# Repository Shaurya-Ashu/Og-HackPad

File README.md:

# Og-HackPad
Hello guys it's an Og HackPad for blueprint hack club . It controls the music and the vibe of the room it has three keyboard switches, 16 RGB LED and a volume controller with a small oled, displaying the name of the song .It's all controlled by XIAO R2040 the "BRAINS" and powered by US PC

# who am I?
Oh this is SHAURYA , I am a young inventor and passionate about cool robotic stuff so like I build multiple projects in my pass but not anything creative as cool as this one it's pretty damn cool. You know like RGB matrix flying up and down on with the song flow that's good.

# component used / BOM

| No. | Component | Qty | 
| --- | --------- | --- |
| 1   | XIAO R2040 | 1  |
| 2   | MX-Cherry switches | 3 |
| 3   | EC11 Rotary encoders | 1 |
| 4   | 0.91 inch OLED | 1 |
| 5   | SK6812 MINI-E LEDs | 16 |
| 6   | 3D PRINTED CASE  | 1 |
| 7   | PCB              | 1 |
| 8   | M3x16mm screws   | 4 |
| 9   | M3x5mx4mm heatset inserts | 4 |

# schematic 
So here are all the connections

--> The three switches are connected respectively to D10 D9 & D8 <br>
--> The rotary encoder is connected to D1 & D2 <br>
--> The old is connected to SCL & SDA respectively <br>
--> The RGB light is connected to D0 <br>

# PCB 
I have designed the PCB in KiCad
Finding all the models and footprint for a headache, but at last it's all done.

# CAD 
I have used fusion education for designing the case of my OgHackPack.
It went surprisingly well . It also has a stand so it could sit at 60° angle from the bench.
Here are some of the rendering from fusion and Blender.

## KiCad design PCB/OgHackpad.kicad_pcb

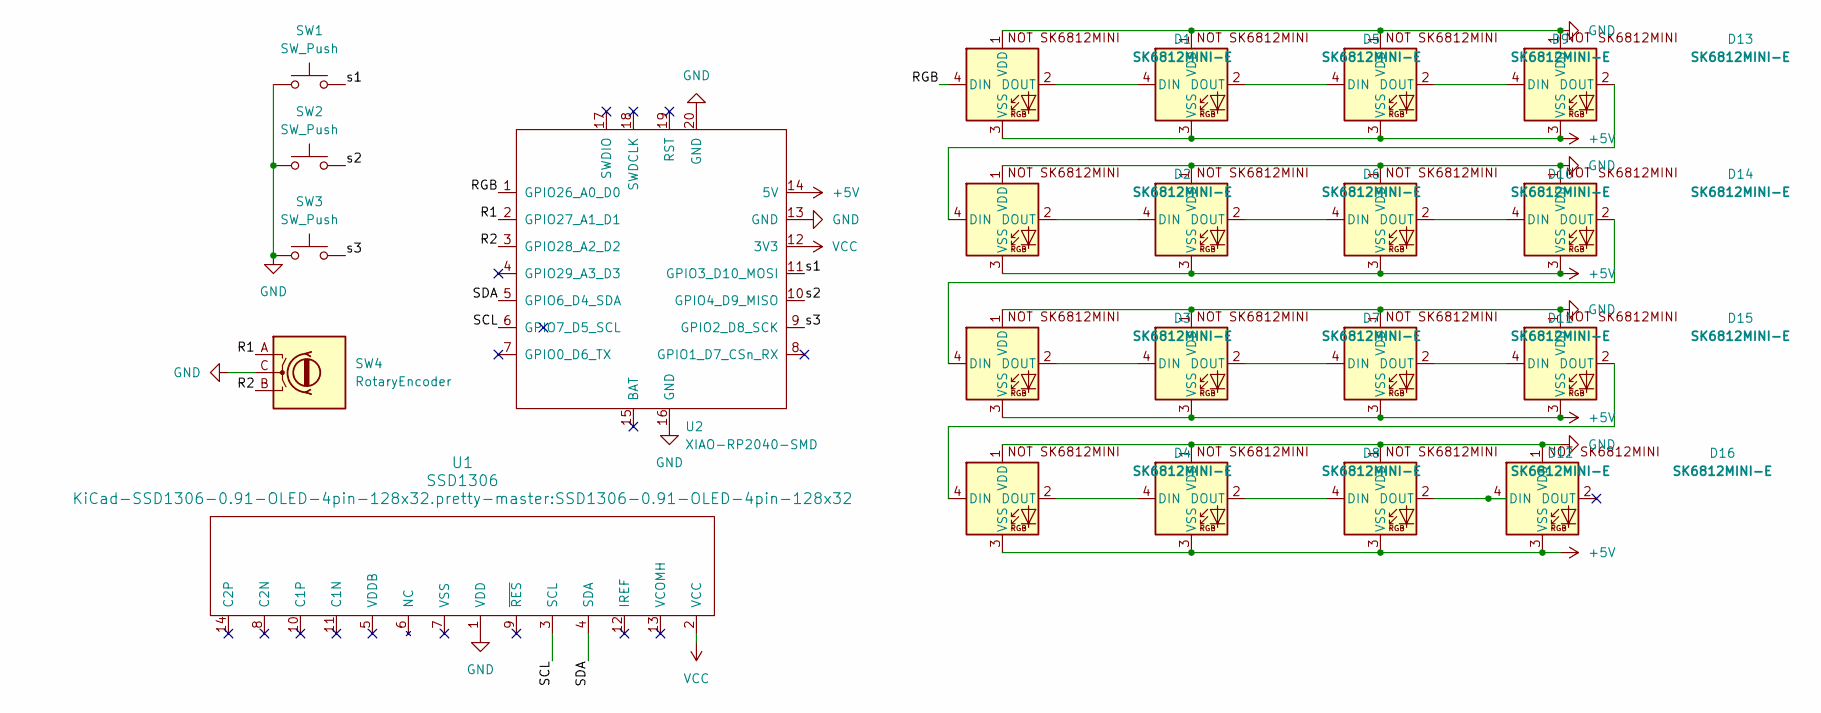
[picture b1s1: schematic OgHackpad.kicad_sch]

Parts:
D1, D2, D3, D4, D5, D6, D7, D8, D9, D10, D11, D12, D13, D14, D15, D16: SK6812MINI-E; SK6812MINI-E_fixed
SW1, SW2, SW3: SW_Push; SW_Cherry_MX_1.00u_PCB
SW4: RotaryEncoder; RotaryEncoder_Alps_EC11E-Switch_Vertical_H20mm
U1: SSD1306; SSD1306-0.91-OLED-4pin-128x32
U2: XIAO-RP2040-SMD

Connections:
+5V: D1.3 (VSS), D2.3 (VSS), D3.3 (VSS), D4.3 (VSS), D5.3 (VSS), D6.3 (VSS), D7.3 (VSS), D8.3 (VSS), D9.3 (VSS), D10.3 (VSS), D11.3 (VSS), D12.3 (VSS), D13.3 (VSS), D14.3 (VSS), D15.3 (VSS), D16.3 (VSS), U2.14 (5V)
/<NO NET>: D1.4 (DIN), SW4.A, U2.1 (GPIO26_A0_D0), U2.2 (GPIO27_A1_D1)
/R2: SW4.B, U2.3 (GPIO28_A2_D2)
/SCL: U1.3 (SCL), U2.6 (GPIO7_D5_SCL)
/SDA: U1.4 (SDA), U2.5 (GPIO6_D4_SDA)
/s1: SW1.2, U2.11 (GPIO3_D10_MOSI)
/s2: SW2.2, U2.10 (GPIO4_D9_MISO)
/s3: SW3.2, U2.9 (GPIO2_D8_SCK)
GND: D1.1 (VDD), D2.1 (VDD), D3.1 (VDD), D4.1 (VDD), D5.1 (VDD), D6.1 (VDD), D7.1 (VDD), D8.1 (VDD), D9.1 (VDD), D10.1 (VDD), D11.1 (VDD), D12.1 (VDD), D13.1 (VDD), D14.1 (VDD), D15.1 (VDD), D16.1 (VDD), SW1.1, SW2.1, SW3.1, SW4.C, U1.1 (VDD), U2.13 (GND), U2.16 (GND), U2.20 (GND)
unnamed: D1.2 (DOUT), D5.4 (DIN)
unnamed: D2.2 (DOUT), D6.4 (DIN)
unnamed: D3.2 (DOUT), D7.4 (DIN)
unnamed: D4.2 (DOUT), D8.4 (DIN)
unnamed: D5.2 (DOUT), D9.4 (DIN)
unnamed: D6.2 (DOUT), D10.4 (DIN)
unnamed: D10.2 (DOUT), D14.4 (DIN)
unnamed: D7.2 (DOUT), D11.4 (DIN)
unnamed: D11.2 (DOUT), D15.4 (DIN)
unnamed: D8.2 (DOUT), D12.4 (DIN)
unnamed: D12.2 (DOUT), D16.4 (DIN)
unnamed: D9.2 (DOUT), D13.4 (DIN)
unnamed: D2.4 (DIN), D13.2 (DOUT)
unnamed: D3.4 (DIN), D14.2 (DOUT)
unnamed: D4.4 (DIN), D15.2 (DOUT)
VCC: U1.2 (VCC), U2.12 (3V3)

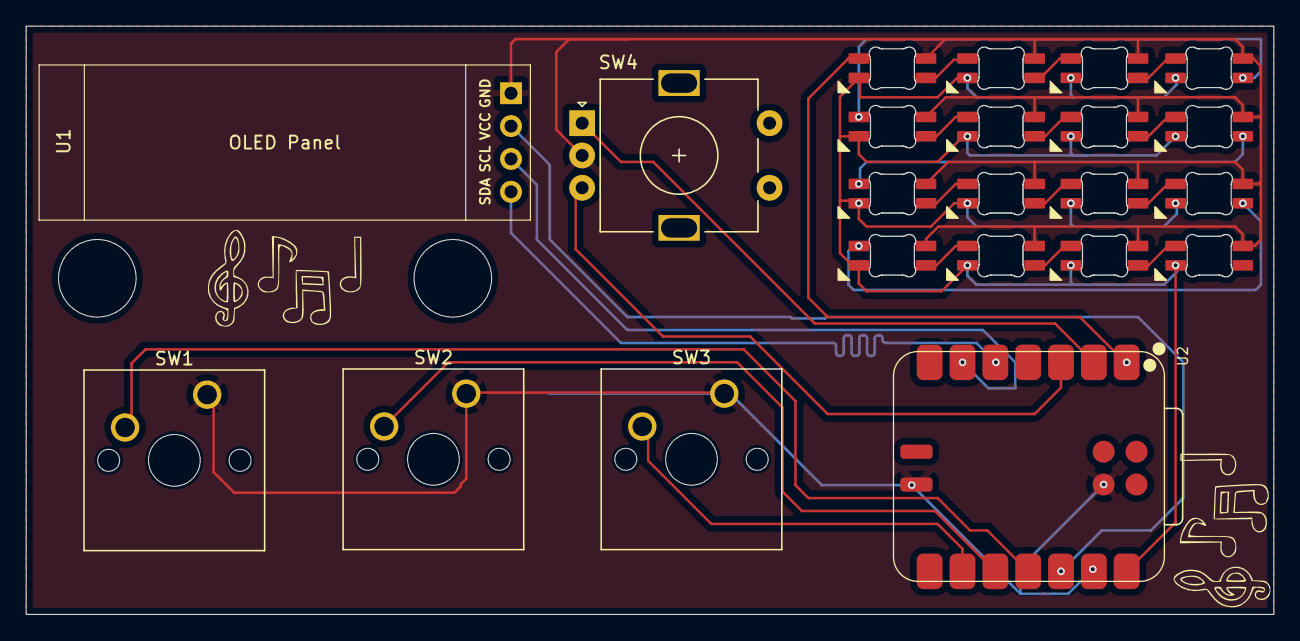
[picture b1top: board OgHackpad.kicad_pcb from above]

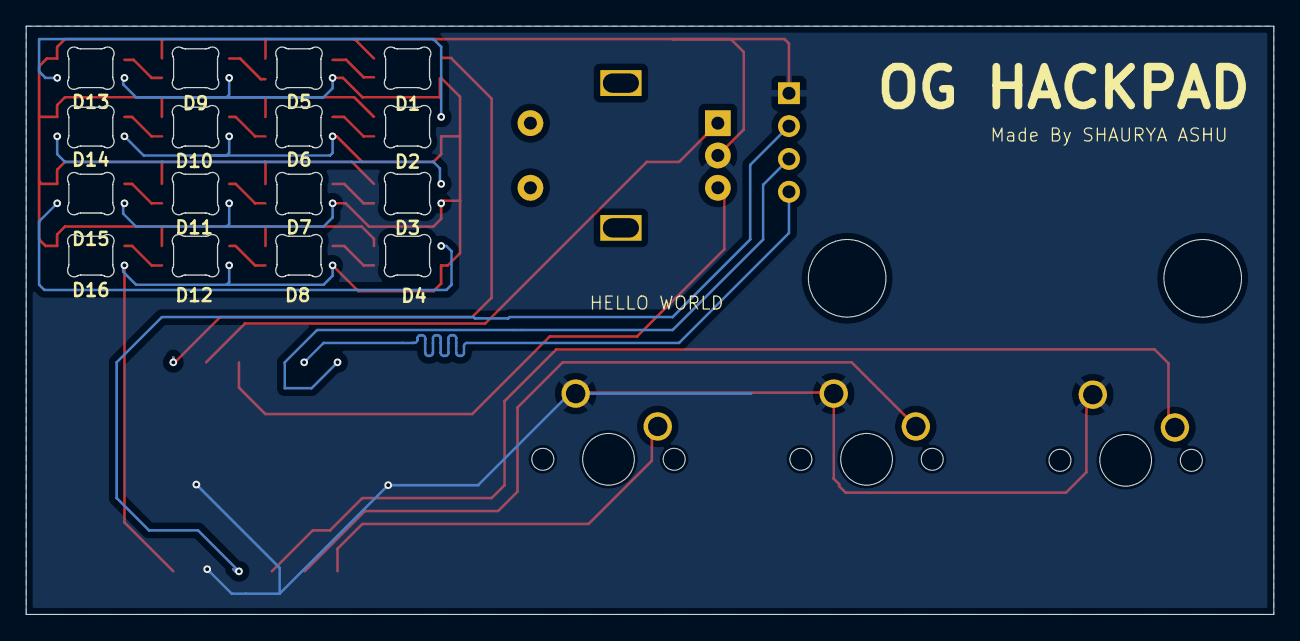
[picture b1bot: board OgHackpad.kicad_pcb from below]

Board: 2 copper layers, 96.5 x 45.5 mm, 22 parts (16 on the bottom side), 25 nets.

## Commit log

2026-01-27 Add keyboard firmware with LED and media key support
    Implement a keyboard firmware with LED visualizer and media controls.
2026-01-27 Create h
2026-01-27 Create CAD
2026-01-27 Create A
2026-01-27 Create B
2026-01-27 Create c
2026-01-27 Create D
2026-01-27 Add BOM for OgHackPad components
2026-01-28 Revise README with project details and images
    Updated project description and added images.
2026-01-28 Improve README with project details and images
    Updated README.md to enhance project description and image references.
2026-01-29 Add M3x16mm screws and heatset inserts to README
